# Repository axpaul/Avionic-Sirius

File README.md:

# Avionic-Sirius
*Sirius experimental rocket avionic (On-board electronics), Version 2024 launched at C'space*

*CC BY-NC-SA 4.0, Copyright 2023 Miailhe Paul, all rights reserved*

.png)

# MotorShield Controller

Le **MotorShield Controller** est une carte d'actionneur conçue pour piloter deux moteurs DC. Elle intègre des circuits en pont en H et des capteurs de courant basés sur des résistances shunt, permettant la détection d'événements, la protection contre les surintensités, le contrôle PWM, ainsi que l'indication visuelle de la direction de rotation des moteurs.

---

## Composants principaux

### 1. **Hex Schmitt-Trigger Inverter (74HC14)**
- **Description** : Inverseur logique avec seuils Schmitt pour améliorer l'immunité aux bruits.  
- **Caractéristiques** :
  - Fonctionne avec des signaux LSTTL, CMOS, NMOS, et TTL.
  - Plage de tension de fonctionnement : 2.0V à 6.0V.
  - Immunité élevée au bruit et faible courant d'entrée.

---

### 2. **Optocoupleurs (ACPL-214)**
- **Description** : Optocoupleurs à gain élevé pour une isolation électrique optimale.  
- **Caractéristiques** :
  - Isolation de tension jusqu’à 3000 VRMS.

---

### 3. **Data Converter Isolator (ADuM1281)**
- **Description** : Isolateur numérique double canal pour la transmission de données.  
- **Caractéristiques** :
  - Fonctionne avec une alimentation de 3.3V.
  - Débit de données jusqu'à 100 Mbps.
  - Faible délai de propagation (23 ns).

---

### 4. **INA381A et INA381B – Détection de surintensité**
- **Description** : Amplificateurs de détection de courant avec comparateurs intégrés.  
- **Caractéristiques** :
  - Détection de courants d’entrée entre 10 mA et 3 A.
  - Seuils configurables pour les surintensités (par ex. : 1A).
  - Fonctionnement avec une tension de 3.3V.
  - Intègre une résistance de shunt de 22 mΩ pour la détection.

---

### 5. **DRV8872 – Pilote de moteur DC brossé avec rapport d’erreurs**
- **Description** : Pilote pour moteurs DC avec contrôle PWM.  
- **Caractéristiques** :
  - Plage de tension : 6.5V à 45V.
  - Courant supporté jusqu’à 3.6A.
  - Intègre des protections (UVLO, OCP, TSD) et un rapport d'état des erreurs.
  - Supporte les modes veille et actif avec contrôle de la direction et de la vitesse via PWM.

---

### 6. **Indicateurs LED de direction du moteur**
- **Description** : Circuit simple avec LEDs et résistances pour indiquer la direction de rotation du moteur.  
- **Caractéristiques** :
  - Confirmation visuelle de la rotation du moteur sans connexion supplémentaire.
  - Permet de tester et de vérifier facilement la logique de contrôle.

---

### 7. **Configuration en pont (JP5)**
- **Description** : Jumper configurable pour définir les fonctionnalités d'entrée ou de sortie.  
- **Caractéristiques** :
  - Évite les conflits d’assignation en définissant clairement les modes de fonctionnement.
 
## Licence

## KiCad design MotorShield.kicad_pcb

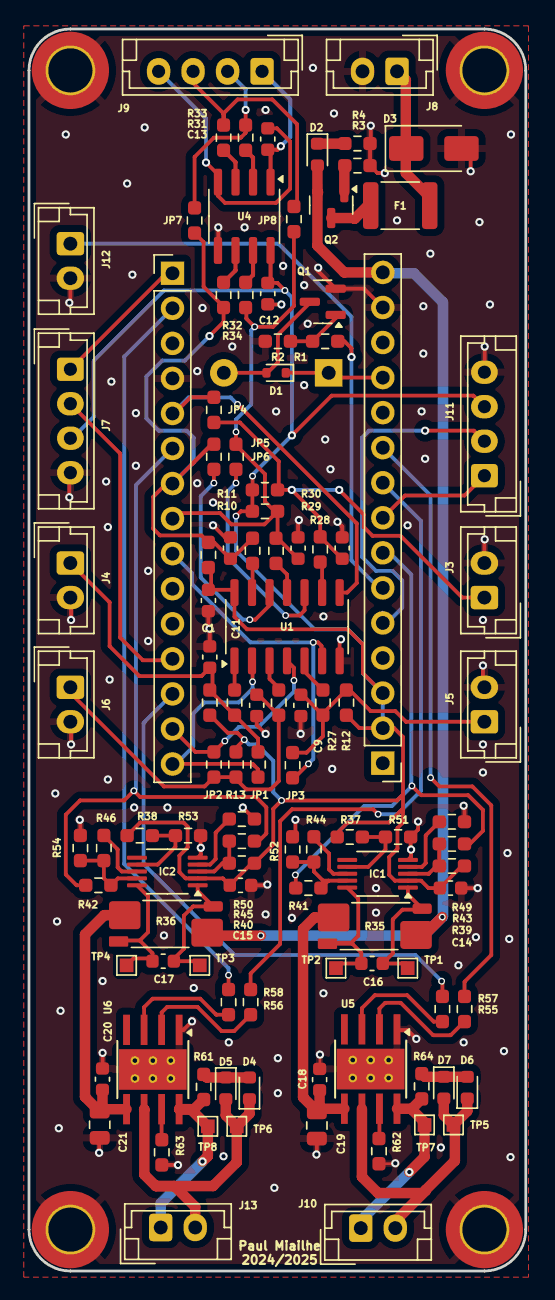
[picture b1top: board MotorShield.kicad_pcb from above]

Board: 4 copper layers, 36.0 x 90.0 mm, 109 parts (1 on the bottom side), 75 nets.

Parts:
BZ1: Buzzer; Buzzer_12x9.5RM7.6
C1, C12, C13, C14, C15, C18, C20: 100nF; C_0603_1608Metric
C6, C7, C8, C9, C10, C11: 1uF; C_0603_1608Metric
C16, C17: NC; C_0603_1608Metric
C19, C21: 47uF; C_0805_2012Metric
D1: 1N4148WT; D_SOD-523
D2: LED; LED_0603_1608Metric
D3: SMAJ14A; D_SMA
D4, D6: LED-R; LED_0603_1608Metric
D5, D7: LED-G; LED_0603_1608Metric
F1: Polyfuse; Fuse_1812_4532Metric
IC1, IC2: INA381; VSSOP-10_3x3mm_P0.5mm
J1, J2: Conn_01x15_Socket; PinHeader_1x15_P2.54mm_Vertical
J3, J4, J5, J6, J8, J10, J12, J13: Conn_01x02; JST_EH_B2B-EH-A_1x02_P2.50mm_Vertical
J7, J9, J11: Conn_01x04; JST_EH_B4B-EH-A_1x04_P2.50mm_Vertical
JP1, JP2, JP3, JP4, JP5, JP6, JP7, JP8: SolderJumper; R_0603_1608Metric_Pad0.98x0.95mm_HandSolder
Q1: BSS138; SOT-23
Q2: FDN360P; SOT-23
R1, R3, R31, R32, R33, R34, R41, R42, R43, R45, R49, R50, R55, R56, R57, R58, R62, R63: 0R; R_0603_1608Metric_Pad0.98x0.95mm_HandSolder
R2, R39, R40, R51, R53: 10k; R_0603_1608Metric_Pad0.98x0.95mm_HandSolder
R4: 1k; R_0603_1608Metric_Pad0.98x0.95mm_HandSolder
R9, R10, R11, R12, R13, R14, R17, R22, R27, R28, R29, R30: 10K; R_0603_1608Metric_Pad0.98x0.95mm_HandSolder
R35, R36: 22mR; R_Shunt_Vishay_WSK2512_6332Metric_T1.19mm
R37, R38: 20k; R_0603_1608Metric_Pad0.98x0.95mm_HandSolder
R44, R46: 43k; R_0603_1608Metric_Pad0.98x0.95mm_HandSolder
R52, R54: 10M; R_0603_1608Metric_Pad0.98x0.95mm_HandSolder
R61, R64: 750R; R_0603_1608Metric_Pad0.98x0.95mm_HandSolder
TP1, TP2, TP3, TP4, TP5, TP6, TP7, TP8: TestPoint_Probe; TestPoint_Pad_1.0x1.0mm
U1: 74HC14; SOIC-14_3.9x8.7mm_P1.27mm
U4: ADuM1281; SOIC-8_3.9x4.9mm_P1.27mm
U5, U6: DRV8872DDA; Texas_HTSOP-8-1EP_3.9x4.9mm_P1.27mm_EP2.95x4.9mm_Mask2.4x3.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

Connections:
+3.3V: C1.1, C12.1, C14.1, C15.1, IC1.2 (VS+), IC2.2 (VS+), J2.2, J2.3, J7.3, J11.3, R9.1, R10.1, R11.1, R12.1, R13.1, R14.1, R37.2, R38.2, R39.2, R40.2, U1.14 (VCC), U4.8 (VDD2)
+3.3V-EXT: C13.1, J9.1, U4.1 (VDD1)
+5V: BZ1.1 (+), D1.1 (K), J2.12
+BATT: D3.1 (A1), F1.1, J8.1
/ADC9: J2.7, R41.1, R43.1
/ADC15: J1.6, R42.1, R45.1
/Avionic - GPIO/OUT_ISO_N1: JP5.2 (B), U1.10
/Avionic - GPIO/OUT_ISO_N2: JP6.2 (B), U1.12
/ENCODER_1A: J1.1, J7.1
/ENCODER_1B: J1.12, J7.2
/ENCODER_2A: J2.5, J11.2
/ENCODER_2B: J2.8, J11.1
/GPIO/IT_1: J1.15, JP1.2 (B), U1.2
/GPIO/IT_2: J1.14, JP2.2 (B), U1.4
/GPIO/IT_3: J1.9, JP3.2 (B), U1.6
/GPIO/IT_4: J1.5, JP4.2 (B), U1.8
/GPIO/IT_5: J2.10, R57.1
/GPIO/IT_6: J2.9, R58.1
/IN_GPIO/IT_1: C11.1, J4.1, JP1.1 (A), R14.2, R17.2
/IN_GPIO/IT_2: C10.1, J6.1, JP2.1 (A), R13.2, R22.2
/IN_GPIO/IT_3: C9.1, J5.1, JP3.1 (A), R12.2, R27.2
/IN_GPIO/IT_4: C8.1, J3.1, JP4.1 (A), R11.2, R28.2
/OUTA_M1: D6.1 (K), D7.2 (A), J10.2, TP5.1, U5.6 (OUT1)
/OUTA_M2: D4.1 (K), D5.2 (A), J13.2, TP6.1, U6.6 (OUT1)
/OUTB_M1: J10.1, R64.1, TP7.1, U5.8 (OUT2)
/OUTB_M2: J13.1, R61.1, TP8.1, U6.8 (OUT2)
/PWM_1: J1.13, R55.1
/PWM_2: J1.2, R56.1
/UART1-RX: C6.1, J1.7, JP6.1 (A), JP7.2 (B), R9.2, R30.2, R34.2
/UART1-RX-EXT: J9.2, JP7.1 (A), R31.1
/UART1-TX: C7.1, J1.8, JP5.1 (A), JP8.2 (B), R10.2, R29.2, R32.2
/UART1-TX-EXT: J9.3, JP8.1 (A), R33.1
/UART2-STLINK: J2.6, J12.1, R1.1
GND: C1.2, C6.2, C7.2, C8.2, C9.2, C10.2, C11.2, C12.2, C14.2, C15.2, C18.2, C19.2, C20.2, C21.2, D3.2 (A2), IC1.5 (GND), IC2.5 (GND), J1.4, J2.14, J3.2, J4.2, J5.2, J6.2, J7.4, J8.2, J11.4, J12.2, Q1.2 (S), R2.1, R3.2, R4.2, R49.1, R50.1, R51.1, R52.1, R53.1, R54.1, R62.1, R63.1, U1.7 (GND), U4.5 (GND2), U5.1 (GND), U5.9 (GND), U6.1 (GND), U6.9 (GND)
GNDD-EXT: C13.2, J9.4, U4.4 (GND1)
unnamed: BZ1.2 (-), D1.2 (A), Q1.3 (D)
unnamed: D2.1 (K), R4.1
unnamed: D4.2 (A), D5.1 (K), R61.2
unnamed: D6.2 (A), D7.1 (K), R64.2
unnamed: IC1.8 (CMPIN), R44.2
unnamed: IC1.7 (CMPREF), R37.1, R51.2
unnamed: C16.1, IC1.1 (IN+), R35.3, TP1.1
unnamed: C16.2, IC1.10 (IN-), R35.2, TP2.1
unnamed: IC1.4 (RESET), R49.2
unnamed: IC1.9 (VOUT), R41.2, R44.1, R52.2
unnamed: IC1.3 (~ALERT), R39.1, R43.2
unnamed: IC2.8 (CMPIN), R46.2
unnamed: IC2.7 (CMPREF), R38.1, R53.2
unnamed: C17.1, IC2.1 (IN+), R36.3, TP3.1
unnamed: C17.2, IC2.10 (IN-), R36.2, TP4.1
unnamed: IC2.4 (RESET), R50.2
unnamed: IC2.9 (VOUT), R42.2, R46.1, R54.2
unnamed: IC2.3 (~ALERT), R40.1, R45.2
unnamed: Q1.1 (G), R1.2, R2.2
unnamed: F1.2, Q2.3 (D)
unnamed: Q2.1 (G), R3.1
unnamed: R17.1, U1.1
unnamed: R22.1, U1.3
unnamed: R27.1, U1.5
unnamed: R28.1, U1.9
unnamed: R29.1, U1.11
unnamed: R30.1, U1.13
unnamed: R32.1, U4.7 (VIA)
unnamed: R33.2, U4.3 (VIB)
unnamed: R31.2, U4.2 (VOA)
unnamed: R34.1, U4.6 (VOB)
unnamed: R55.2, U5.3 (IN1)
unnamed: R57.2, U5.2 (IN2)
unnamed: R62.2, U5.7 (ISEN)
unnamed: R56.2, U6.3 (IN1)
unnamed: R58.2, U6.2 (IN2)
unnamed: R63.2, U6.7 (ISEN)
VCC: D2.2 (A), J2.15, Q2.2 (S), R35.4, R36.4
VCCM1: C18.1, C19.1, R35.1, U5.5 (VM)
VCCM2: C20.1, C21.1, R36.1, U6.5 (VM)

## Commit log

2024-09-25 Add images

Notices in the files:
README.md:
Licence:
https://github.com/axpaul/Avionic-Marsaut1/blob/main/Cc-by-nc-sa_icon.svg.png
